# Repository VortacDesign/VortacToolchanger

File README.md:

# VortacToolchanger
Modular toolchanger system for 3D printers – designed for VORON-style machines. Includes mechanical files, wiring guides, firmware configuration and setup scripts.

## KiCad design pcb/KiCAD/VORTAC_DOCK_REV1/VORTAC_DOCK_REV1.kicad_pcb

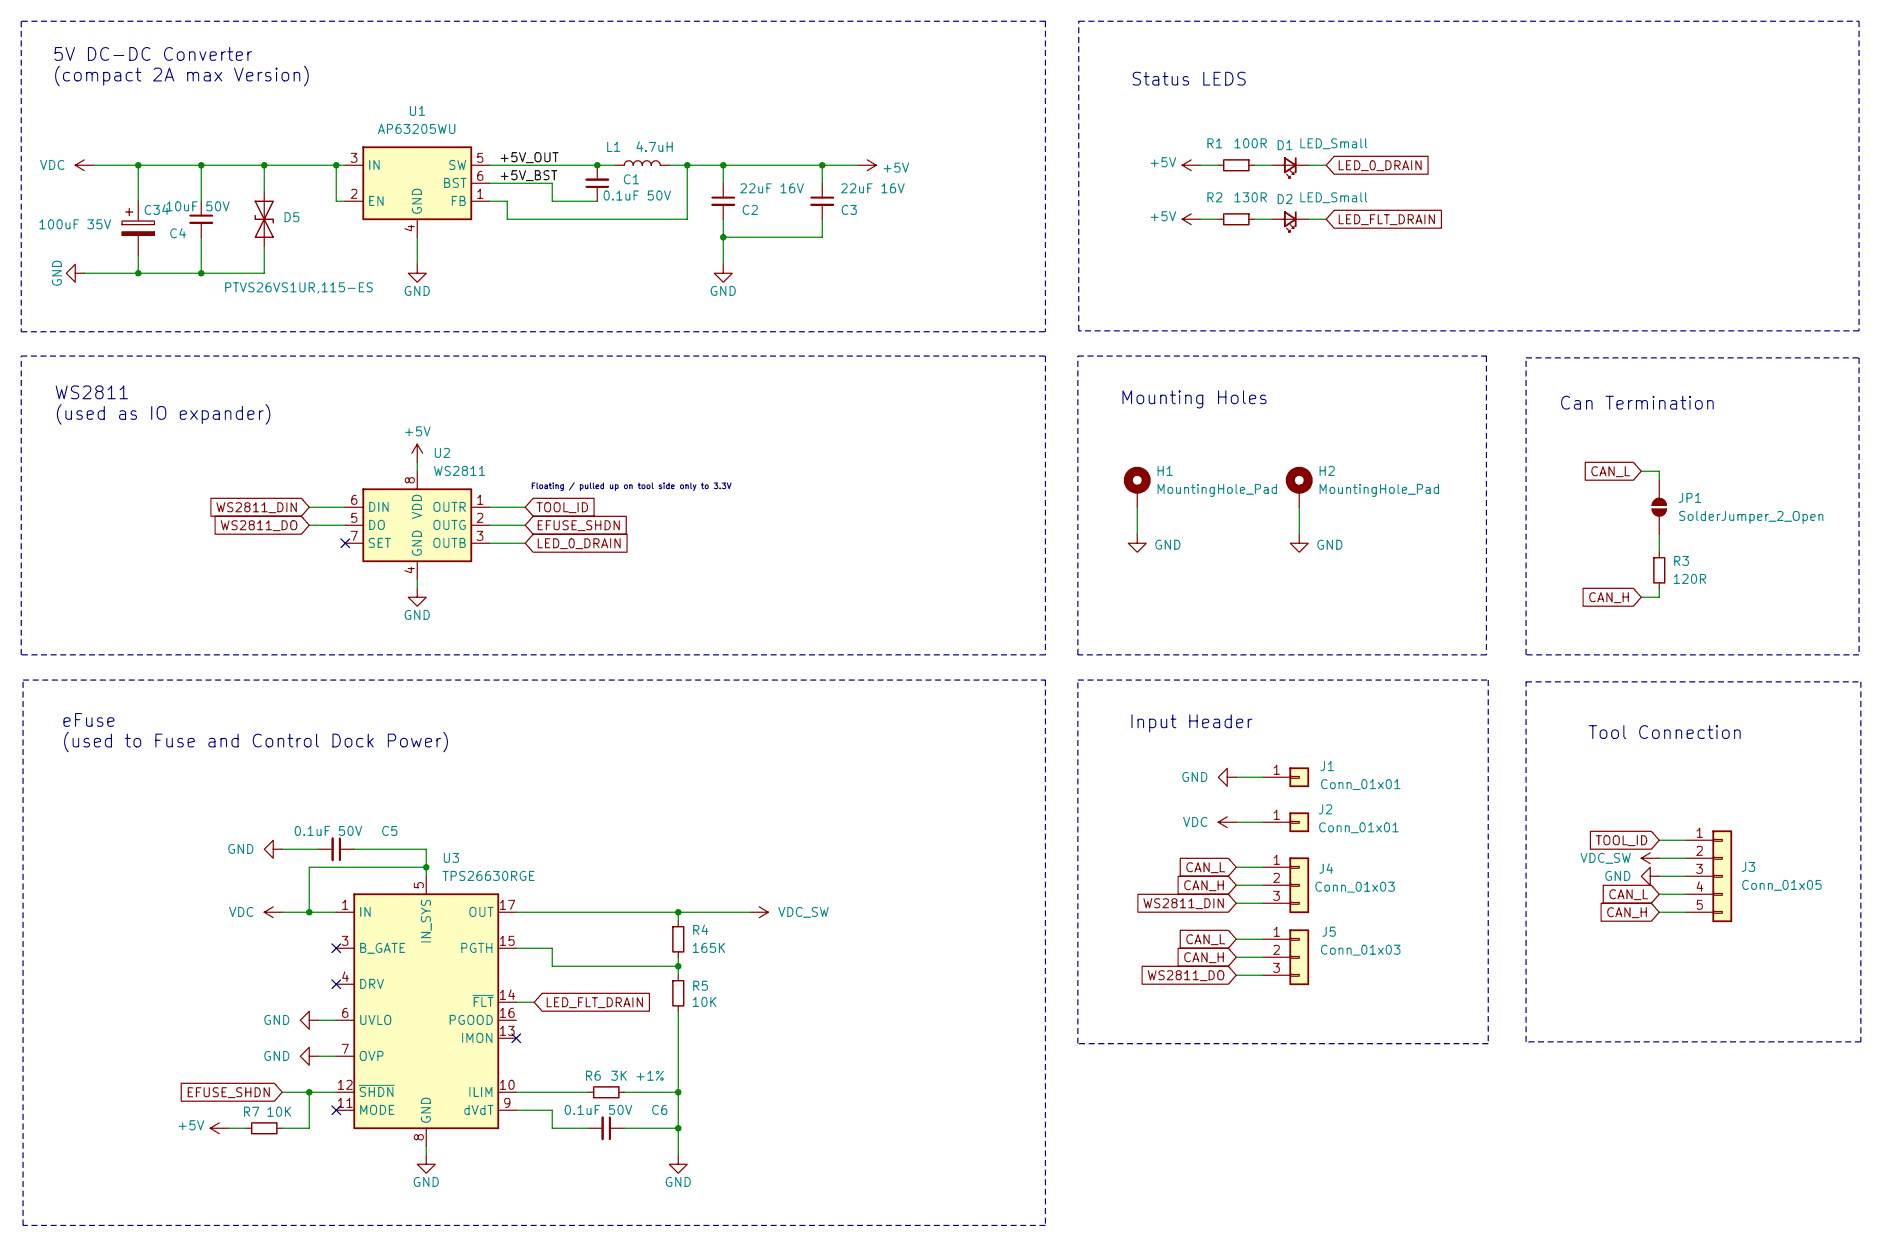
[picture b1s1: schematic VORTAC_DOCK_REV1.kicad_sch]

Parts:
C1, C5, C6: 0.1uF 50V; C_0402_1005Metric; LCSC C5182432
C2, C3: 22uF 16V; C_0603_1608Metric; LCSC C2762594
C4: 10uF 50V; C_0805_2012Metric; LCSC C440198
C34: 100uF 35V; CP_Elec_6.3x7.7; LCSC C2983388
D1: LED_Small; LED_0402_1005Metric; LCSC C130724
D2: LED_Small; LED_0402_1005Metric; LCSC C130719
D5: PTVS26VS1UR,115-ES; D_SOD-123F; LCSC C41409305
H1, H2: MountingHole_Pad; MountingHole_2.2mm_M2_ISO7380_Pad
J1: Conn_01x01; Dock_Solderpoint_02x01_GND
J2: Conn_01x01; Dock_Solderpoint_02x01_VCC
J3: Conn_01x05; mill-max-0881-1-15-20-82-14-11-0_LandingPads_Simple_01x05
J4, J5: Conn_01x03; Solderpoint_01x03_Data
JP1: SolderJumper_2_Open; SolderJumper-2_P1.3mm_Open_RoundedPad1.0x1.5mm
L1: 4.7uH; L_Wurth_WE-LQSH-2512; LCSC C5832360
R1: 100R; R_0402_1005Metric; LCSC C106232
R2: 130R; R_0402_1005Metric; LCSC C477610
R3: 120R; R_0402_1005Metric; LCSC C114758
R4: 165K; R_0402_1005Metric; LCSC C38706
R5, R7: 10K; R_0402_1005Metric; LCSC C60490
R6: 3K +1%; R_0402_1005Metric; LCSC C137987
U1: AP63205WU; TSOT-23-6; LCSC C2071056
U2: WS2811; SOT-23-8; 8mm pitch; LCSC C5446692
U3: TPS26630RGE; Texas_RGE0024H_VQFN-24-1EP_4x4mm_P0.5mm_EP2.7x2.7mm_Thermal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; LCSC C1850276

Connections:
+5V: C2.1, C3.1, L1.2, R1.2, R2.2, R7.1, U1.1 (FB), U2.8 (VDD)
/+5V_BST: C1.1, U1.6 (BST)
/+5V_OUT: C1.2, L1.1, U1.5 (SW)
CAN_H: J3.5, J4.2, J5.2, R3.2
CAN_L: J3.4, J4.1, J5.1, JP1.2 (B)
EFUSE_SHDN: R7.2, U2.2 (OUTG), U3.12 (~SHDN)
GND: C2.2, C3.2, C4.2, C5.2, C6.1, C34.2, D5.2 (A2), H1.1, H2.1, J1.1, J3.3, R5.2, R6.2, U1.4 (GND), U2.4 (GND), U3.6 (UVLO), U3.7 (OVP), U3.8 (GND), U3.25 (GND)
LED_0_DRAIN: D1.1 (K), U2.3 (OUTB)
LED_FLT_DRAIN: D2.1 (K), U3.14 (~FLT)
unnamed: D1.2 (A), R1.1
unnamed: D2.2 (A), R2.1
unnamed: JP1.1 (A), R3.1
unnamed: R6.1, U3.10 (ILIM)
unnamed: R4.2, R5.1, U3.15 (PGTH)
unnamed: C6.2, U3.9 (dVdT)
TOOL_ID: J3.1, U2.1 (OUTR)
VDC: C4.1, C5.1, C34.1, D5.1 (A1), J2.1, U1.2 (EN), U1.3 (IN), U3.1 (IN), U3.2 (IN), U3.5 (IN_SYS)
VDC_SW: J3.2, R4.1, U3.17 (OUT), U3.18 (OUT)
WS2811_DIN: J4.3, U2.6 (DIN)
WS2811_DO: J5.3, U2.5 (DO)

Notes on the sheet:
Tool Connection
Floating / pulled up on tool side only to 3.3V
Status LEDS
Mounting Holes
WS2811 (used as IO expander)
Can Termination
eFuse (used to Fuse and Control Dock Power)
5V DC-DC Converter (compact 2A max Version)
Input Header

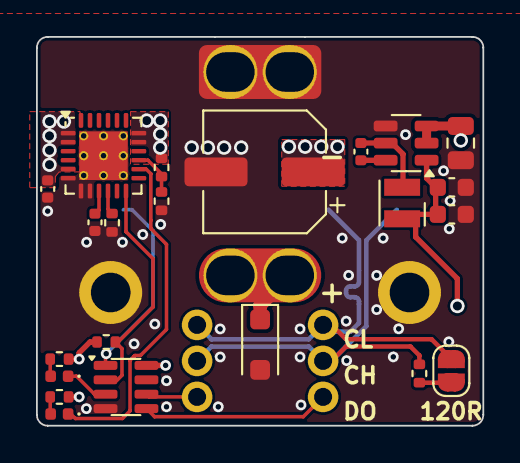
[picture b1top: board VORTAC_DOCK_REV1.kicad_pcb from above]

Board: 4 copper layers, 24.8 x 21.6 mm, 29 parts (1 on the bottom side), 20 nets.

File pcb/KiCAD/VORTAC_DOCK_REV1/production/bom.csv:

Designator,Footprint,Quantity,Value,LCSC Part #
"C1, C5, C6",0402,3,0.1uF 50V,C5182432
"C2, C3",0603,2,22uF 16V,C2762594
C34,CP_Elec_6.3x7.7,1,100uF 35V,C2983388 
C4,0805,1,10uF 50V,C440198
D1,0402,1,LED_Small,C130724
D2,0402,1,LED_Small,C130719
D5,D_SOD-123F,1,"PTVS26VS1UR,115-ES",C41409305
L1,L_Wurth_WE-LQSH-2512,1,4.7uH,C5832360
R1,0402,1,100R,C106232
R2,0402,1,130R,C477610
R3,0402,1,120R,C114758
R4,0402,1,165K,C38706
"R5, R7",0402,2,10K,C60490
R6,0402,1,3K +1%,C137987
U1,TSOT-23-6,1,AP63205WU,C2071056
U2,SOT-23-8; 8mm pitch,1,WS2811,C5446692
U3,Texas_RGE0024H_VQFN-24-1EP_4x4mm_P0.5mm_EP2.7x2.7mm_ThermalVias,1,TPS26630RGE,C1850276

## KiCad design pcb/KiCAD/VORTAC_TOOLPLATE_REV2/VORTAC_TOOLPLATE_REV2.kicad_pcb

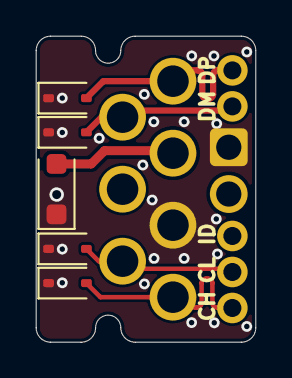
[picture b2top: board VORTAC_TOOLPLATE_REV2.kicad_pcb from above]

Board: 4 copper layers, 12.2 x 17.0 mm, 9 parts (0 on the bottom side), 7 nets.

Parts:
D1, D2: UDD32C24L01; D_SOD-323
D3, D4: SD05; D_SOD-323
D9: PTVS26VS1UR,115-ES; D_SOD-123F
J1: Conn_01x07; mill-max-0881-1-15-20-82-14-11-0_LandingPads_ContactPad_PTH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
J2: Conn_01x02; Toolplate_Solderpoint_01x02_Power_Small
J4: Conn_01x02; Toolplate_Solderpoint_01x02_Data_Small
J5: Conn_01x03; Toolplate_Solderpoint_01x03_Data_Small

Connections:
CAN_H: D2.2 (A2), J1.7, J5.3
CAN_L: D1.2 (A2), J1.6, J5.2
GND: D1.1 (A1), D2.1 (A1), D3.1 (A1), D4.1 (A1), D9.1 (A1), J1.5, J2.1
TOOL_ID: J1.4, J5.1
USB_90_D+: D3.2 (A2), J1.1, J4.1
USB_90_D-: D4.2 (A2), J1.2, J4.2
VDC: D9.2 (A2), J1.3, J2.2

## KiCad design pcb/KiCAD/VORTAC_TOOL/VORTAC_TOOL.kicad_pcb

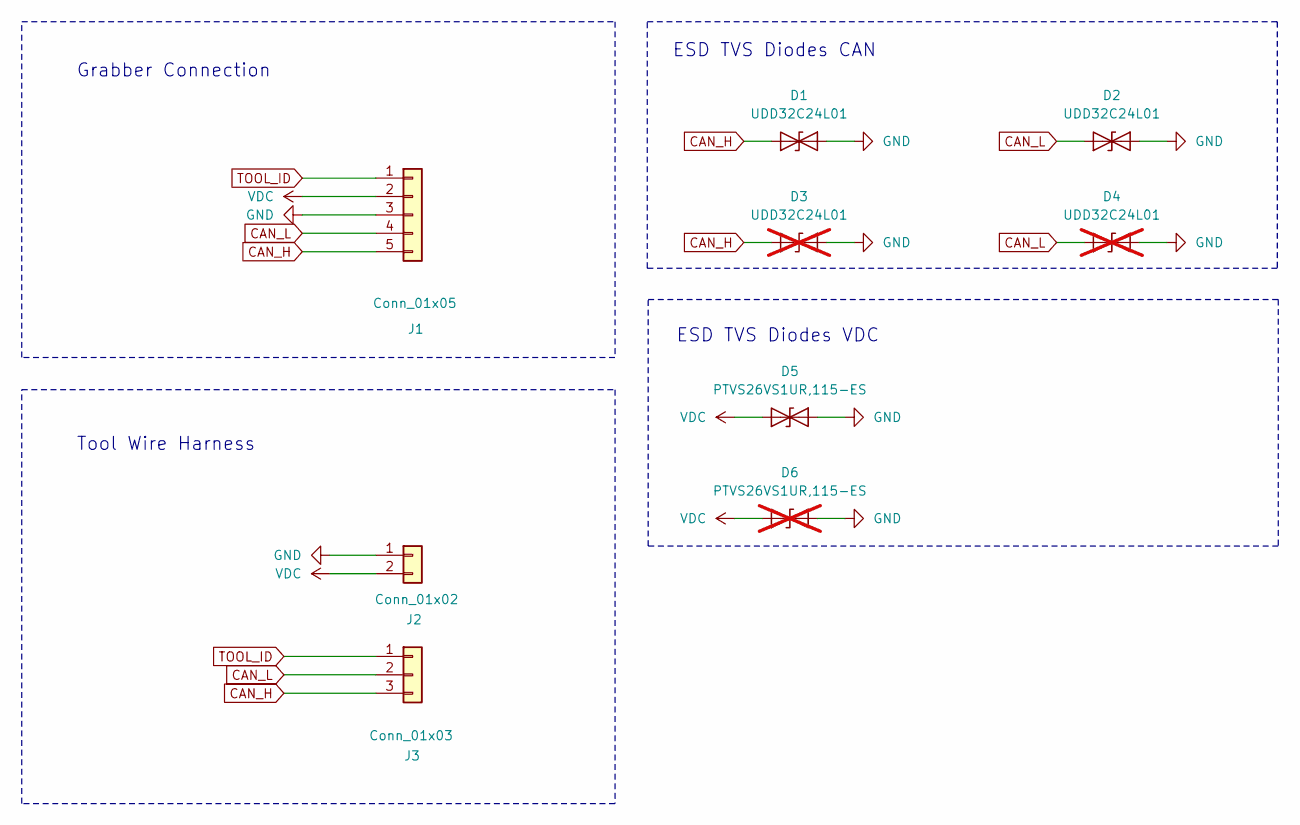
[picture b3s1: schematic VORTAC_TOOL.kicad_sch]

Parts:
D1, D2: UDD32C24L01; D_SOD-323; LCSC C19188728
D3, D4: UDD32C24L01; D_SOD-323; LCSC C19188728; not fitted
D5: PTVS26VS1UR,115-ES; D_SOD-123F; LCSC C41409305
D6: PTVS26VS1UR,115-ES; D_SOD-123F; LCSC C41409305; not fitted
J1: Conn_01x05; mill-max-0881-1-15-20-82-14-11-0_LandingPads_ContactPad_1x5
J2: Conn_01x02; Toolplate_Solderpoint_01x02_Power_Small
J3: Conn_01x03; Toolplate_Solderpoint_01x03_Data_Small

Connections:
CAN_H: D1.2 (A2), D3.2 (A2), J1.5, J3.3
CAN_L: D2.2 (A2), D4.2 (A2), J1.4, J3.2
GND: D1.1 (A1), D2.1 (A1), D3.1 (A1), D4.1 (A1), D5.1 (A1), D6.1 (A1), J1.3, J2.1
TOOL_ID: J1.1, J3.1
VDC: D5.2 (A2), D6.2 (A2), J1.2, J2.2

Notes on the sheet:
Grabber Connection
ESD TVS Diodes VDC
Tool Wire Harness
ESD TVS Diodes CAN

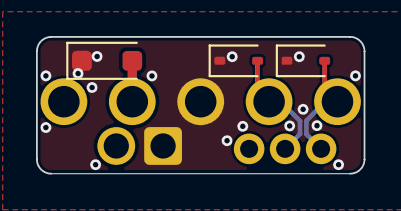
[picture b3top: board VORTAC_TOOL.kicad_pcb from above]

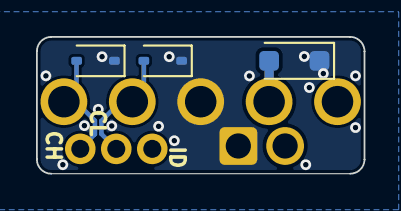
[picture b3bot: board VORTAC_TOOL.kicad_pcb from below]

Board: 4 copper layers, 18.2 x 7.6 mm, 9 parts (6 on the bottom side), 5 nets.

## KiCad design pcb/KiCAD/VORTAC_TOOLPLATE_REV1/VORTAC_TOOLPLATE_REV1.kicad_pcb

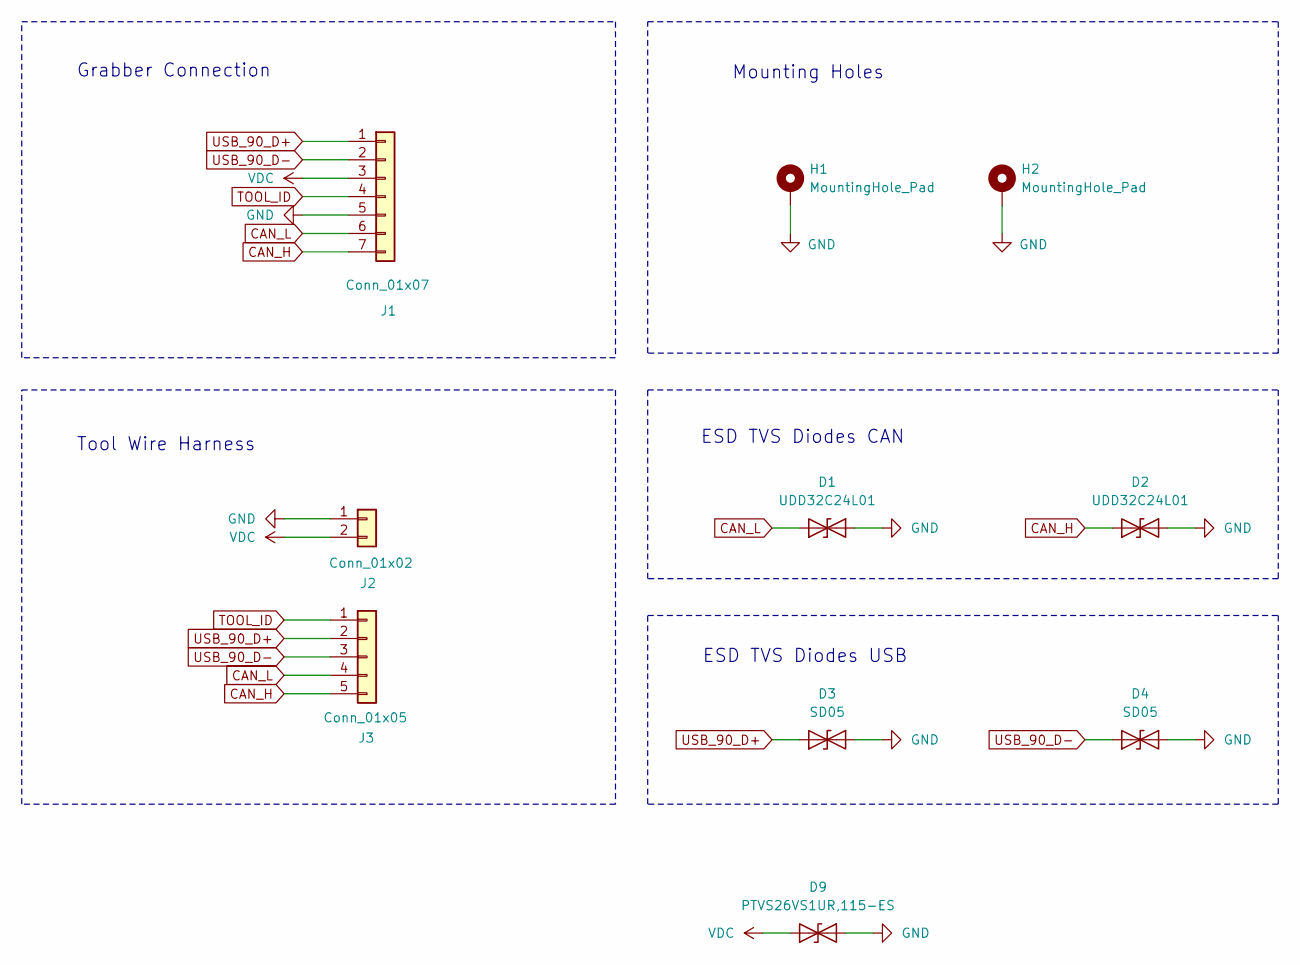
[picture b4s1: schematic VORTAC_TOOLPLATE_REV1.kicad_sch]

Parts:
D1, D2: UDD32C24L01; D_SOD-323; LCSC C19188728
D3, D4: SD05; D_SOD-323; LCSC C502527
D9: PTVS26VS1UR,115-ES; D_SOD-123F; LCSC C41409305
H1, H2: MountingHole_Pad; MountingHole_2.2mm_M2_Pad_Via_NTR
J1: Conn_01x07; mill-max-0881-1-15-20-82-14-11-0_LandingPads_ContactPad_PTH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
J2: Conn_01x02; Toolplate_Solderpoint_01x02_Power
J3: Conn_01x05; Toolplate_Solderpoint_01x05_Data

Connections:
CAN_H: D2.2 (A2), J1.7, J3.5
CAN_L: D1.2 (A2), J1.6, J3.4
GND: D1.1 (A1), D2.1 (A1), D3.1 (A1), D4.1 (A1), D9.1 (A1), H1.1, H2.1, J1.5, J2.1
TOOL_ID: J1.4, J3.1
USB_90_D+: D3.2 (A2), J1.1, J3.2
USB_90_D-: D4.2 (A2), J1.2, J3.3
VDC: D9.2 (A2), J1.3, J2.2

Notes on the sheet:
Grabber Connection
Tool Wire Harness
ESD TVS Diodes CAN
ESD TVS Diodes USB
Mounting Holes

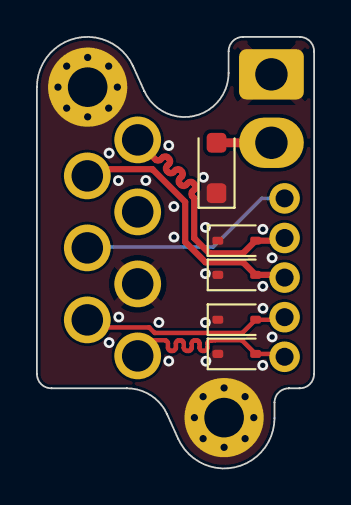
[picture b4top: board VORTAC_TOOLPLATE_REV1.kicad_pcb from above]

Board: 4 copper layers, 15.4 x 24.0 mm, 10 parts (0 on the bottom side), 7 nets.

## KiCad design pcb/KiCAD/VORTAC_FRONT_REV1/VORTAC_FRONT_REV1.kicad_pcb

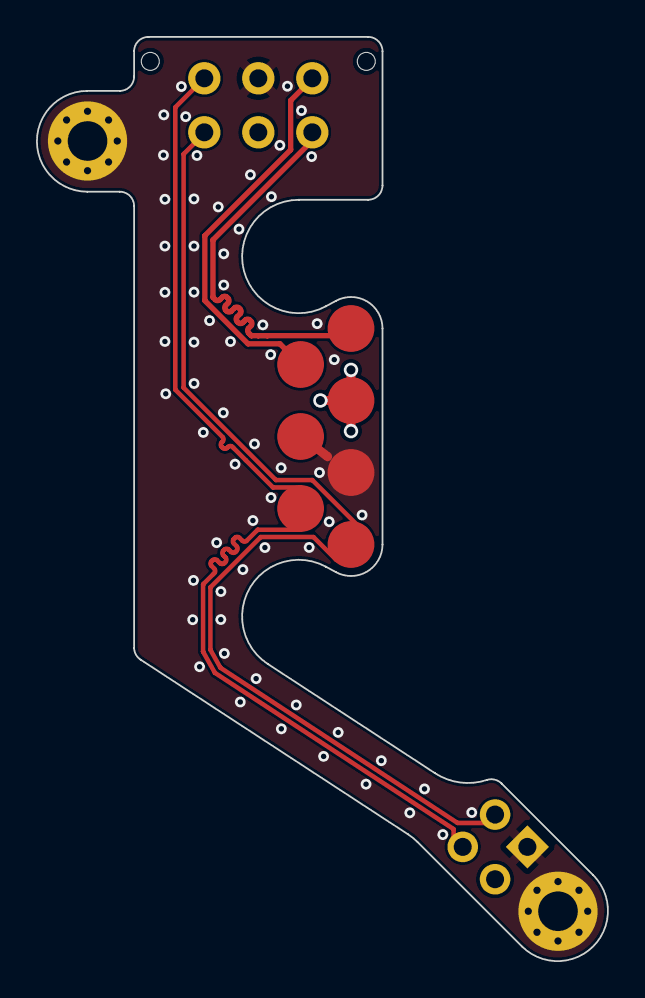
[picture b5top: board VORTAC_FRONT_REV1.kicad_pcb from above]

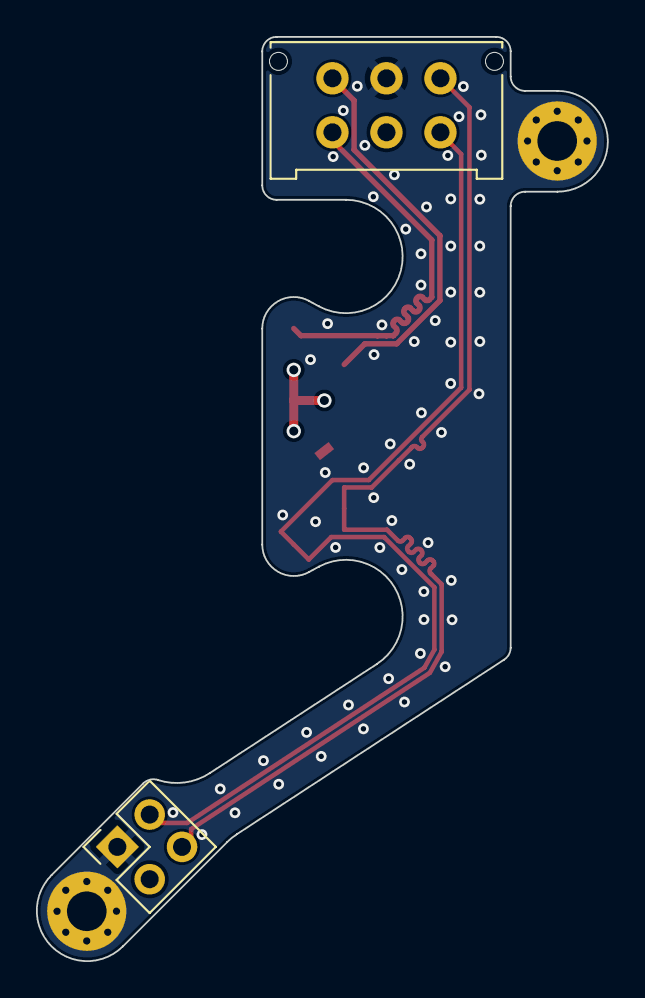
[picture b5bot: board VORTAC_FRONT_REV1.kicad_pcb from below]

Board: 4 copper layers, 31.7 x 51.3 mm, 6 parts (2 on the bottom side), 7 nets.

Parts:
H1, H2: MountingHole_Pad; MountingHole_2.2mm_M2_Pad_Via_NTR
J1: Conn_02x02_Odd_Even; PinSocket_2x02_P2.54mm_Vertical
J2: Conn_02x03_Odd_Even; Molex_Micro-Fit_3.0_43045-0612_2x03_P3.00mm_Vertical
J3: Conn_01x07; mill-max-0881-1-15-20-82-14-11-0_LandingPads_Simple
NT1: NetTie_2; NetTie-2_SMD_Pad0.5mm

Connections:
CAN_H: J1.3, J2.1, J3.7
CAN_L: J1.4, J2.4, J3.6
GND: H1.1, H2.1, J1.1, J2.5, J3.5, NT1.2
TOOL_ID: J3.4, NT1.1
USB_D+: J2.3, J3.1
USB_D-: J2.6, J3.2
VDC: J1.2, J2.2, J3.3

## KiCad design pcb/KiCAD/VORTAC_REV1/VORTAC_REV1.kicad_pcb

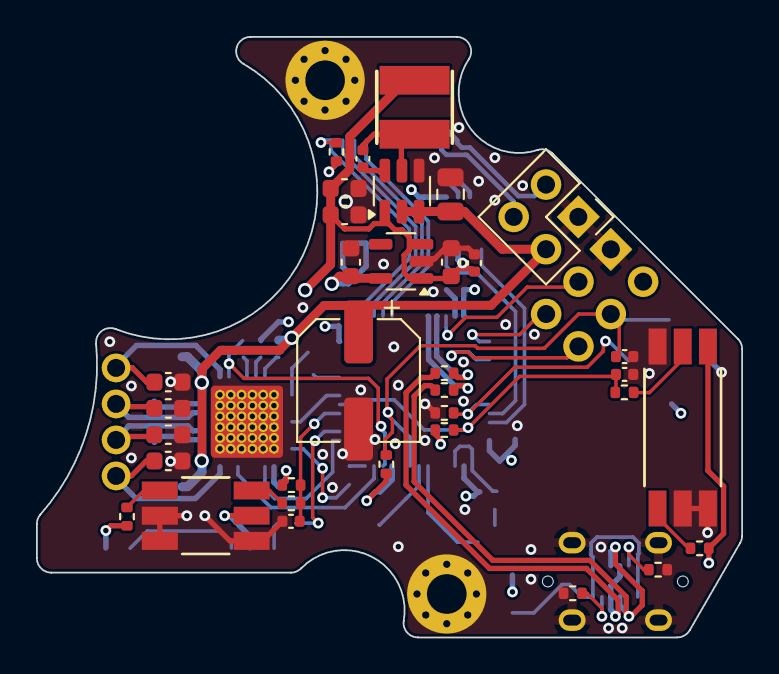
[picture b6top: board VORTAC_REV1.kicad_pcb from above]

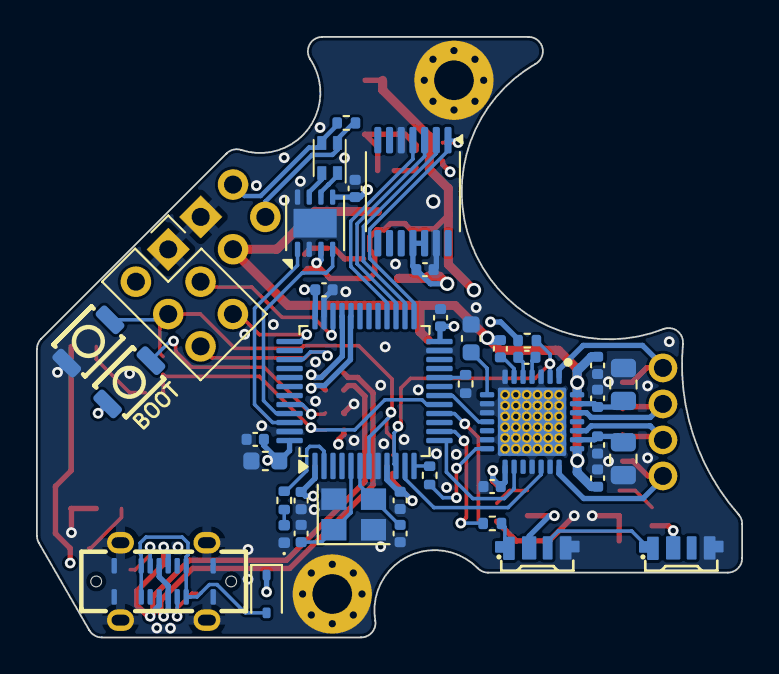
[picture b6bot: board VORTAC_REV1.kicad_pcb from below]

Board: 4 copper layers, 39.2 x 33.4 mm, 77 parts (40 on the bottom side), 58 nets.

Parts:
C1, C4, C6, C9: 470pF 100V; C_0603_1608Metric
C2, C10, C13, C15, C17, C19, C21, C24, C25, C26, C28, C29, C33, C35, C36, C37, C38, C39: 0.1uF 50V; C_0402_1005Metric
C3, C8: 1uF 16V; C_0603_1608Metric
C22, C40: 4.7uF 50V; C_0603_1608Metric
C23: 22nF 50V; C_0402_1005Metric
C27: 10uF 50V; C_0805_2012Metric
C30, C31: 22uF 16V; C_0603_1608Metric
C34: 100uF 35V; CP_Elec_6.3x7.7
C42, C43: 16pF 50V; C_0402_1005Metric
D5: D_Schottky; D_SOD-323
D6: LED_Small; LED_0402_1005Metric
H1, H2: MountingHole_Pad; MountingHole_2.2mm_M2_Pad_Via_NTR
IC1: TMC2209-LA; tmc_2209_package
J1: DEBUG; PinSocket_2x03_P2.54mm_Vertical
J3: Conn_02x02_Odd_Even; PinHeader_2x02_P2.54mm_Vertical
J14: 918-418K2023S40001; USB-C-SMD_TYPEC-303-ACP16
J15: STEPPER; Motor_Hand_Wire_pads
L1: Common Choke; L_CommonModeChoke_Coilcraft_0805USB
L3: 4.7uH; IND-SMD_L4.0-W4.0_FNR40XXS
LED1, LED2: SK6812SIDE-A-RVS; LED-SMD_4P-L4.0-W1.6-L
R1, R13, R15: 1K; R_0402_1005Metric
R2, R8, R9, R11, R12, R14, R32: 10K; R_0402_1005Metric
R3, R4: 5.1K; R_0402_1005Metric
R5, R6: 330R; R_0402_1005Metric
R7, R10: 115R; R_0402_1005Metric
R30, R34: 0.68R 1%; R_0805_2012Metric
R35, R36, R38: 22R; R_0402_1005Metric
SW1: Boot; KEY-SMD_B3U-1000PM
SW2: Reset; KEY-SMD_B3U-1000PM
U1: TLV73333PDBV; SOT-23-5
U2: STM32F103C8T6; LQFP-48_7x7mm_P0.5mm
U3: EE-SX4320; SENSOR_EE-SX4320_OMR
U5: AS5047D; TSSOP-14_4.4x5mm_P0.65mm
U6: AP63205WU; TSOT-23-6
U7: EE-SX4350; SENSOR_EE-SX3350_OMR
U8: TJA1044GTK/3Z; HVSON-8-1EP_3x3mm_P0.65mm_EP1.6x2.4mm
Y1: 8MHz; Crystal_SMD_3225-4Pin_3.2x2.5mm

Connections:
+3V3: C8.1, C15.2, C21.1, C33.2, C35.1, C36.2, C37.2, C38.2, C39.2, C40.2, IC1.15 (VCC_IO), J1.2, R2.1, R8.1, R9.2, R14.2, R32.2, SW1.2, U1.5 (OUT), U2.1 (VBAT), U2.9 (VDDA), U2.24 (VDD), U2.36 (VDD), U2.48 (VDD), U5.11 (VDD), U5.12 (VDD3V3), U8.5 (VIO)
+5V: C3.1, C17.1, C30.1, C31.1, D5.1 (K), L3.2, LED1.2 (VDD), LED2.2 (VDD), R5.1, R6.1, U1.1 (IN), U1.3 (EN), U3.5 (VCC), U6.1 (FB), U7.4 (VCC), U8.3 (VCC)
/Logic/+5V_BST: C28.1, U6.6 (BST)
/Logic/+5V_OUT: C28.2, L3.1, U6.5 (SW)
/MCU/CAN_H_CHOKE: L1.4, U8.7 (CANH)
/MCU/CAN_L_CHOKE: L1.1, U8.6 (CANL)
/MCU/DAMPEND_USB_D+: R36.2, U2.33 (PA12)
/MCU/DAMPEND_USB_D-: R35.2, U2.32 (PA11)
AS_MISO: U2.27 (PB14), U5.3 (MISO)
AS_MOSI: U2.28 (PB15), U5.4 (MOSI)
AS_NSS: R14.1, U2.25 (PB12), U5.1 (~CS)
AS_SCK: U2.26 (PB13), U5.2 (CLK)
BOOT_0: R11.1, SW1.1, U2.44 (BOOT0)
BOOT_1: R12.1, U2.20 (PB2)
CAN_H: J3.3, L1.3, R10.1
CAN_L: J3.4, L1.2, R10.2
CAN_RX: U2.45 (PB8), U8.4 (RXD)
CAN_TX: U2.46 (PB9), U8.1 (TXD)
DEBUG_SWCLK: J1.5, U2.37 (PA14)
DEBUG_SWDIO: J1.3, U2.34 (PA13)
DEBUG_SWO: J1.6, U2.39 (PB3)
ENDSTOP_X: C25.2, R8.2, R15.1, U2.17 (PA7)
ENDSTOP_Z: C19.2, R1.1, R2.2, U2.16 (PA6)
GND: C1.2, C2.2, C3.2, C4.2, C6.2, C8.2, C9.2, C10.2, C13.2, C15.1, C17.2, C19.1, C21.2, C22.2, C25.1, C26.1, C27.2, C29.1, C30.2, C31.2, C33.1, C34.2, C35.2, C36.1, C37.1, C38.1, C39.1, C40.1, C42.2, C43.2, D6.1 (K), H1.1, H2.1, IC1.3 (GND), IC1.7 (SPREAD), IC1.9 (MS1_AD0), IC1.10 (MS2_AD1), IC1.13 (CLK), IC1.18 (GND), IC1.20 (STDBY), IC1.29 (GNDPAD), J1.1, J3.1, J14.A1 (GND), J14.A12 (GND), J14.B1 (GND), J14.B12 (GND), J14.S1 (SHIELD), LED1.4 (GND), LED2.4 (GND), R3.1, R4.1, R11.2, R12.2, R30.1, R34.1, SW2.2, U1.2 (GND), U2.8 (VSSA), U2.23 (VSS), U2.35 (VSS), U2.47 (VSS), U3.2 (CATHODE), U3.3 (CATHODE), U3.4 (GND), U5.5 (TST), U5.13 (GND), U6.4 (GND), U7.2 (NC), U7.3 (CATHODE), U7.6 (GND), U8.2 (GND), U8.8 (STB), U8.9 (EP), Y1.2, Y1.4
HSE_OSC_IN: C42.1, U2.5 (PD0), Y1.1
HSE_OSC_OUT: C43.1, U2.6 (PD1), Y1.3
LED_0: R38.2, U2.2 (PC13)
LED_DIN: LED1.1 (DIN), R7.1
NRST: C13.1, J1.4, R9.1, SW2.1, U2.7 (NRST)
unnamed: D5.2 (A), J14.A4 (VBUS), J14.A9 (VBUS), J14.B4 (VBUS), J14.B9 (VBUS)
unnamed: D6.2 (A), R38.1
unnamed: C22.1, IC1.8 (5VOUT)
unnamed: C23.1, IC1.5 (CPI)
unnamed: C23.2, IC1.4 (CPO)
unnamed: C24.1, IC1.6 (VCP)
unnamed: J14.A5 (CC1), R4.2
unnamed: J14.B5 (CC2), R3.2
unnamed: LED1.3 (DOUT), LED2.1 (DIN)
unnamed: R13.1, U2.12 (PA2)
unnamed: R7.2, U2.14 (PA4)
unnamed: R6.2, U3.1 (ANODE)
unnamed: R1.2, U3.6 (OUTPUT)
unnamed: R5.2, U7.1 (ANODE)
unnamed: R15.2, U7.5 (OUTPUT)
STEP_1_A1: C4.1, IC1.24 (OA1), J15.2
STEP_1_A2: C1.1, IC1.21 (OA2), J15.1
STEP_1_B1: C6.1, IC1.26 (OB1), J15.3
STEP_1_B2: C9.1, IC1.1 (OB2), J15.4
TMC_BRA: C10.1, IC1.23 (BRA), R34.2
TMC_BRB: C2.1, IC1.27 (BRB), R30.2
TMC_DIAG: IC1.11 (DIAG), U2.18 (PB0)
TMC_DIR: IC1.19 (DIR), U2.11 (PA1)
TMC_ENN: IC1.2 (ENN), R32.1, U2.10 (PA0)
TMC_STEP: IC1.16 (STEP), U2.13 (PA3)
TMC_UART: IC1.14 (PDN_UART), R13.2
USB_D+: J14.A6 (D+), J14.B6 (D+), R36.1
USB_D-: J14.A7 (D-), J14.B7 (D-), R35.1
VDC: C24.2, C26.2, C27.1, C29.2, C34.1, IC1.22 (VS), IC1.28 (VS), J3.2, U6.2 (EN), U6.3 (IN)

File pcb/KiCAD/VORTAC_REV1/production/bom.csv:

Designator,Footprint,Quantity,Value,LCSC Part #
"C1, C4, C6, C9",0603,4,470pF 100V,C326973
"C10, C13, C15, C17, C19, C2, C21, C24, C25, C26, C28, C29, C33, C35, C36, C37, C38, C39",0402,18,0.1uF 50V,C5182432
"C22, C40",0603,2,4.7uF 50V,C513577
C23,0402,1,22nF 50V,C107026
C27,0805,1,10uF 50V,C440198
"C3, C8",0603,2,1uF 16V,C106248
"C30, C31",0805,2,22uF 16V,C2762594
C34,CP_Elec_6.3x7.7,1,100uF 35V,C2983388 
"C42, C43",0402,2,16pF 50V,C513591
D5,D_SOD-323,1,D_Schottky,C7420331
D6,0402,1,LED_Small,C130724
IC1,tmc_2209_package,1,TMC2209-LA,C2150710
J1,PinSocket_2x03_P2.54mm_Vertical,1,DEBUG,C541853
J14,USB-C-SMD_TYPEC-303-ACP16,1,918-418K2023S40001,C720628
J15,Motor_Hand_Wire_pads,1,STEPPER,
J3,PinHeader_2x02_P2.54mm_Vertical,1,Conn_02x02_Odd_Even,C7501273
L1,L_CommonModeChoke_Coilcraft_0805USB,1,Common Choke,C3029267
L3,IND-SMD_L4.0-W4.0_FNR40XXS,1,4.7uH,C167874
"LED1, LED2",LED-SMD_4P-L4.0-W1.6-L,2,SK6812SIDE-A-RVS,C2890037
Q3,SOT-363_SC-70-6,1,BSS138AKDW,C5224287
"R1, R13, R15",0402,3,1K,C106235
"R10, R7",0402,2,115R,C295872
"R11, R12, R14, R16, R2, R32, R8, R9",0402,8,10K,C60490
"R3, R4",0402,2,5.1K,C105872
"R30, R34",0805,2,0.22R 1%,C346768
"R35, R36, R38",0402,3,22R,
"R5, R6",0402,2,330R,C6117577
SW1,KEY-SMD_B3U-1000PM,1,Boot,C231329
SW2,KEY-SMD_B3U-1000PM,1,Reset,C231329
U1,SOT-23-5,1,TLV73333PDBV,C408972
U2,LQFP-48_7x7mm_P0.5mm,1,STM32F103C8T6,C8734
U3,SENSOR_EE-SX4320_OMR,1,EE-SX4320,C469129
U5,TSSOP-14_4.4x5mm_P0.65mm,1,AS5047D,C2693743
U6,TSOT-23-6,1,AP63205WU,C2071056
U7,SENSOR_EE-SX3350_OMR,1,EE-SX3350,C7470740
U8,HVSON-8-1EP_3x3mm_P0.65mm_EP1.6x2.4mm,1,TJA1044GTK/3Z,C2157795
Y1,Crystal_SMD_3225-4Pin_3.2x2.5mm,1,8MHz,C5261255

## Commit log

2025-06-08 init with PCB-Files
2025-06-08 added Submodule
2025-06-09 some stls
2025-06-15 Cleaned up old and intermediate files from pcb repo
2025-10-04 Added Dock PCB
2025-10-04 init Vortac_Tool
2025-10-04 new Footprints and replaced chonky connectors
2025-10-27 Vortac Dock rough component placement #NO-JIRA
2025-10-29 Check Lcsc numbers
2025-10-29 Updated PCB Outline and Refferences based on CAD
2025-10-30 updateting Custom Foorprints to show Ref**
2025-10-30 Update SolderPads
2025-10-30 removed SolderMask
2025-10-30 Routed Vortac Dock PCB REV1
2025-11-01 Robi
2025-11-01 update footprint
2025-11-01 Added VORTAC_TOOLPLATE_REV2
    Modified VORTAC_TOOL
2025-11-02 (Hopefully) Finalized DOCK, TOOL and TOOLPLATE REV2 for ordering
2025-11-02 Production Files
2026-04-22 Doc Rev1 revision
2026-04-23 Added Dock STLs and updated Dock PCB STEP to match the newest itteration
